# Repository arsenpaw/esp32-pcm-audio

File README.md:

# ESP32 WLED LED Driver

> **The active hardware is [`hardware/`](hardware/).** The earlier rev A design
> is kept read-only in [`hardware_deprecated/`](hardware_deprecated/) and is no longer maintained.

## Active board: `hardware/`

A WS2812B LED strip driver with:

- USB-C programming, a DC barrel jack, and screw-terminal inputs.
- Two strip outputs with a 74xx125 level shifter.
- A slide switch for 5 V or 12 V strips.
- A relay and a blade fuse.
- An SPH0641 PDM MEMS microphone (MK1).

We fit an **ESP32-S3-WROOM-1-N4** in the footprint drawn for the ESP32-S2-SOLO, because the S2
can't read PDM microphones. The pad-by-pad check is in [shop.md](shop.md).

### WLED pin map

| Function | GPIO |
|---|---|
| LED strip 1 data | 17 |
| LED strip 2 data | 21 |
| Relay | 7 |
| Status LED | 2 |
| Button (BOOT) | 0 |
| Microphone (PDM) | CLK 5, DATA 6 |

- KiCad project: `hardware/PCB/iot_led_strip_pcb.kicad_pro` (KiCad 10).
- Shopping list: [shop.md](shop.md). It uses the cheapest in-stock part for each line.
- Case: `hardware/case/`.

### Checks from the command line

```bash
kicad-cli sch erc hardware/PCB/iot_led_strip_pcb.kicad_sch
```

```bash
kicad-cli pcb drc hardware/PCB/iot_led_strip_pcb.kicad_pcb
```

On macOS, `kicad-cli` lives at `/Applications/KiCad/KiCad.app/Contents/MacOS/kicad-cli`.

## Deprecated: `hardware_deprecated/` (rev A)

This was the earlier design: a 66 × 32 mm, 4-layer, USB-C-only board.

- MCU: ESP32-S3-MINI-1.
- Power: a 2 A eFuse.
- Microphone: ICS-43434 I2S.

Its schematic is drawn and the board is routed, but it was never reviewed or ordered. These
documents belong to it:

- [Requirements & proposed design](docs/requirements/wled-audio-board.md)
- [WLED configuration](firmware/wled-config.md)

## Tooling

- **KiCad 10** (developed on 10.0.8).
- **KiCad MCP** for Claude Code:
  [`mixelpixx/KiCAD-MCP-Server`](https://github.com/mixelpixx/KiCAD-MCP-Server) v2.9.0.
  It's vendored as a git submodule at `tools/kicad-mcp-server` and registered in `.mcp.json`.
  One-time setup after cloning needs Node 18+ and KiCad 10 in `/Applications`:

  ```bash
  git submodule update --init
  ```

  ```bash
  ./scripts/setup-mcp.sh
  ```

  Launch Claude Code from the repo root, because `.mcp.json` uses paths relative to it.

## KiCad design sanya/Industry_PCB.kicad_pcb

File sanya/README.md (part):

# Система моніторингу технічного стану двигуна (вібрація / температура / тиск)

Навчальний прототип на окремому мікроконтролері **ATmega328P-AU**. Пристрій вимірює вібрацію (ADXL345), температуру (DS18B20) і тиск (аналоговий датчик 0–5 В), визначає стан NORMAL / WARNING / CRITICAL, сигналізує світлодіодами та зумером і **фізично вимикає навантаження через реле**. Додатково керує вентилятором охолодження (ШІМ).

> ⚠️ Це навчальний пристрій. Він **не сертифікований** для встановлення на реальний трактор чи інший транспортний засіб (немає захисту від load-dump, автомобільного температурного діапазону, випробувань на вібрацію/ЕМС).

## Файли

| Файл | Призначення |
|---|---|
| `Industry_PCB.kicad_pro` | проєкт KiCad 10 (класи кіл, правила DRC) |
| `Industry_PCB.kicad_sch` | принципова схема, 1 аркуш A3; усередині вузлів — провідники, між вузлами — іменовані мітки кіл. Резисторні збірки RN1 і RN2 показано окремими резисторами (RN1A…D, RN2A…D) біля своїх сигналів |
| `Industry_PCB.kicad_pcb` | двошарова плата 90 × 65 мм, повністю розведена |
| `Industry_PCB_schematic.pdf` | схема у PDF |
| `Industry_PCB_pcb.pdf` | плата у PDF (F.Cu, B.Cu, складальний шар) |
| `BOM.csv` | перелік компонентів (згрупований) |
| `_generator/` | Python-скрипти, якими згенеровано схему й плату (`design.py` — компоненти, `gen2.py` — поточна схема з провідниками, `place.py` — розміщення на платі) |
| `_old_ESP32_version/` | попередня версія проєкту (ESP32 DevKit + модулі), збережена без змін |

Проєкт створено у форматі **KiCad 10.0** (перевірено у 10.0.8). Під час першого запуску KiCad запропонує створити глобальні таблиці бібліотек — погодьтеся на стандартні; усі символи також вбудовані в сам файл схеми.

## Що змінено порівняно з попередньою версією

| Було | Стало |
|---|---|
| ESP32 DevKit (готова плата на двох гребінках) | окремий MCU ATmega328P-AU (TQFP-32) з кварцом, розв'язкою, ISP |
| SW-420 (цифровий «датчик вібрації», модуль) | 3-осьовий акселерометр ADXL345 на платі, I2C |
| модуль реле на 3-контактному роз'ємі | реле SRD-12VDC-SL-C на платі + драйвер ULN2003A + клеми NO/COM/NC |
| ACS712 (струм) | вхід тиску 0–5 В із захистом, дільником і RC-фільтром |
| живлення 5 В з гнізда, без захисту | 12 В → PTC → діод → TVS → L7805 (5 В) → MCP1700 (3,3 В) |
| немає вентилятора, кнопок, ISP, тест-точок | вихід вентилятора (ШІМ), RESET, ACK/SET, AVR-ISP-6, 9 тест-точок |

## Блоки схеми

1. **POWER.** Клема J1 (12 В) → самовідновлюваний запобіжник F1 (1,1 А) → діод Шотткі D1 (захист від переполюсування) → TVS D2 (SMBJ15CA) і C1 100 мкФ → L7805 (U1, 5 В) → MCP1700-3302 (U2, 3,3 В). Шина +12V живить лише реле, вентилятор і вхід стабілізатора.
2. **MCU.** ATmega328P-AU працює від **3,3 В на 8 МГц** (кварц Y1 + C6/C7 по 22 пФ). 16 МГц при 3,3 В виходить за межі специфікації, тому обрано 8 МГц; живлення 3,3 В дає пряме узгодження рівнів I2C з ADXL345 без перетворювача. C4/C5 — розв'язка VCC/AVCC, SW1 — RESET, RN2 — підтяжки.
3. **VIBRATION SENSOR.** ADXL345BCCZ (U4), I2C, адреса 0x53 (SDO → GND, CS → VDDIO). Живлення через феритову намистину FB1 і C8. Вихід INT1 заведено на PD2 (INT0). Мікросхема стоїть приблизно за 10 мм від кріпильного отвору H4 — плата кріпиться цим кутом до контрольованого вузла.
4. **TEMPERATURE SENSOR.** Роз'єм J3 (JST-XH, 3 конт.) для виносного DS18B20: 3V3 / DQ / GND. Підтяжка 4,7 кОм (RN2), ESD-діод D8 на лінії даних.
5. **PRESSURE INPUT.** Роз'єм J4: +5V / вхід / GND. Дільник R1/R2 (10k/18k, коефіцієнт 0,643: 5,0 В → 3,21 В), C9 100 нФ (зріз ≈ 250 Гц), BAT54S (D3) обмежує напругу до GND…3,3 В. R1 водночас обмежує струм при перенапрузі. Підходить будь-який датчик 0–5 В або 0,5–4,5 В (тиск оливи, гідравліка).
6. **DISPLAY.** Гніздо J5 під модуль OLED SSD1306 I2C (GND / VCC / SCL / SDA). Дисплей опційний.
7. **USER INTERFACE.** D4 зелений (NORMAL), D5 жовтий (WARNING), D6 червоний (CRITICAL), резисторна збірка RN1 4×330 Ом, кнопка SW2 ACK/SET (внутрішня підтяжка MCU).
8. **ALARM + драйвер.** ULN2003A (U5): канал 1 — реле, канал 2 — активний зумер BZ1 (5 В), канали 3–5 паралельно — вентилятор. Входи ULN мають вбудовані резистори на землю, тому під час скидання MCU всі виходи вимкнені. Вивід COM підключено до +12V — це вбудовані зворотні (flyback) діоди для котушки реле й вентилятора.
9. **RELAY / ACTUATOR.** Реле K1 (SPDT, котушка 12 В) і клема J6 NO/COM/NC. D7 показує стан реле. Логіка fail-safe: у нормі реле **увімкнене**, навантаження живиться через COM–NO; при аварії або зникненні живлення реле відпускає і розриває коло.
10. **FAN CONTROL.** Клема J7 (+12 В / FAN−), ШІМ із PD3 (OC2B) через три канали ULN2003A. Струм вентилятора до 0,6 А.
11. **PROGRAMMING.** Стандартний AVR-ISP-6 (J2).

Логіка роботи (для прошивки): температура висока → вентилятор; вібрація або тиск за критичним порогом → реле вимкнути + зумер + червоний LED; ACK скидає звукову сигналізацію.

## Розподіл виводів MCU (ATmega328P-AU, TQFP-32)

| Вивід | Порт | Коло | Призначення |
|---|---|---|---|
| 1 | PD3 (OC2B) | FAN_PWM | ШІМ вентилятора → U5 IN3–5 |
| 2 | PD4 | ONEWIRE_DQ | DS18B20 |
| 3, 5, 21 | GND | GND | |
| 4, 6 | VCC | +3V3 | розв'язка C4 |
| 7, 8 | PB6, PB7 | XTAL1, XTAL2 | кварц 8 МГц |
| 9 | PD5 | BUZZER_CTRL | зумер → U5 IN2 |
| 10 | PD6 | RELAY_CTRL | реле → U5 IN1, LED D7 |
| 11 | PD7 | BTN_ACK | кнопка ACK/SET (активний 0) |
| 12 | PB0 | LED_GREEN | NORMAL |
| 13 | PB1 | LED_YELLOW | WARNING |
| 14 | PB2 | LED_RED | CRITICAL |
| 15, 16, 17 | PB3, PB4, PB5 | MOSI, MISO, SCK | ISP |
| 18 | AVCC | +3V3 | розв'язка C5, опорна напруга АЦП |
| 23 | PC0 (ADC0) | PRESS_ADC | тиск |
| 27, 28 | PC4, PC5 | SDA, SCL | ADXL345, OLED |
| 29 | PC6 | RESET | SW1, ISP, підтяжка 4,7 кОм |
| 30, 31 | PD0, PD1 | UART_RX, UART_TX | тест-точки TP8, TP9 (налагодження) |
| 32 | PD2 (INT0) | ADXL_INT1 | переривання акселерометра |
| 19, 20, 22, 24–26 | ADC6, AREF, ADC7, PC1–PC3 | — | не використані (резерв) |

Тиск у вольтах на вході: `Vin = ADC / 1023 × 3,3 В / 0,643`.

## Розподіл компонентів: 40 шт.

| Блок | К-сть | Компоненти |
|---|---|---|
| POWER | 9 | C1, C2, C3, D1, D2, F1, J1, U1, U2 |
| MCU | 8 | C4, C5, C6, C7, RN2, SW1, U3, Y1 |
| VIBRATION | 3 | C8, FB1, U4 |
| TEMPERATURE | 2 | D8, J3 |
| PRESSURE | 5 | C9, D3, J4, R1, R2 |
| DISPLAY | 1 | J5 |
| USER INTERFACE | 5 | D4, D5, D6, RN1, SW2 |
| ALARM | 2 | BZ1, U5 |
| RELAY / ACTUATOR | 3 | D7, J6, K1 |
| FAN CONTROL | 1 | J7 |
| PROGRAMMING | 1 | J2 |
| **Разом** | **40** | |

Тест-точки TP1–TP9 і кріпильні отвори H1–H4 — це лише мідні площадки та отвори, у BOM і підрахунок вони не входять. Щоб вкластися в 40 компонентів при повному наборі функцій, резистори світлодіодів і підтяжок зібрано у дві збірки 4×0603, а три транзисторні ключі з діодами замінено однією ULN2003A.

## Перелік компонентів

| Ref | Value | Footprint | MPN | Виробник | Блок |
|---|---|---|---|---|---|
| BZ1 | Buzzer 5V active | Buzzer_12x9.5RM7.6 | TMB12A05 | generic 12x9.5 mm | ALARM |
| C1 | 100uF/35V | CP_Radial_D6.3mm_P2.50mm | ECA-1VM101 | Panasonic | POWER |
| C2 | 10uF/16V | C_0805_2012Metric | CL21A106KOQNNNE | Samsung | POWER |
| C3 | 1uF/16V | C_0603_1608Metric | CL10A105KO8NNNC | Samsung | POWER |
| C4 | 100nF | C_0603_1608Metric | CL10B104KB8NNNC | Samsung | MCU |
| C5 | 100nF | C_0603_1608Metric | CL10B104KB8NNNC | Samsung | MCU |
| C6 | 22pF | C_0603_1608Metric | CL10C220JB8NNNC | Samsung | MCU |
| C7 | 22pF | C_0603_1608Metric | CL10C220JB8NNNC | Samsung | MCU |
| C8 | 100nF | C_0603_1608Metric | CL10B104KB8NNNC | Samsung | VIBRATION |
| C9 | 100nF | C_0603_1608Metric | CL10B104KB8NNNC | Samsung | PRESSURE |
| D1 | SS34 | D_SMA | SS34 | onsemi / MCC | POWER |
| D2 | SMBJ15CA | D_SMB | SMBJ15CA | Littelfuse | POWER |
| D3 | BAT54S | SOT-23 | BAT54S,215 | Nexperia | PRESSURE |
| D4 | GREEN | LED_0805_2012Metric | APT2012SGC | Kingbright | USER INTERFACE |
| D5 | YELLOW | LED_0805_2012Metric | APT2012SYCK | Kingbright | USER INTERFACE |
| D6 | RED | LED_0805_2012Metric | APT2012SRCPRV | Kingbright | USER INTERFACE |
| D7 | ORANGE (RELAY ON) | LED_0805_2012Metric | APT2012SECK | Kingbright | RELAY / ACTUATOR |
| D8 | PESD5V0S1BA | D_SOD-323 | PESD5V0S1BA,115 | Nexperia | TEMPERATURE |
| F1 | 1.1A/16V PTC | Fuse_1812_4532Metric_Pad1.30x3.40mm_HandSolder | MF-MSMF110/16-2 | Bourns | POWER |
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
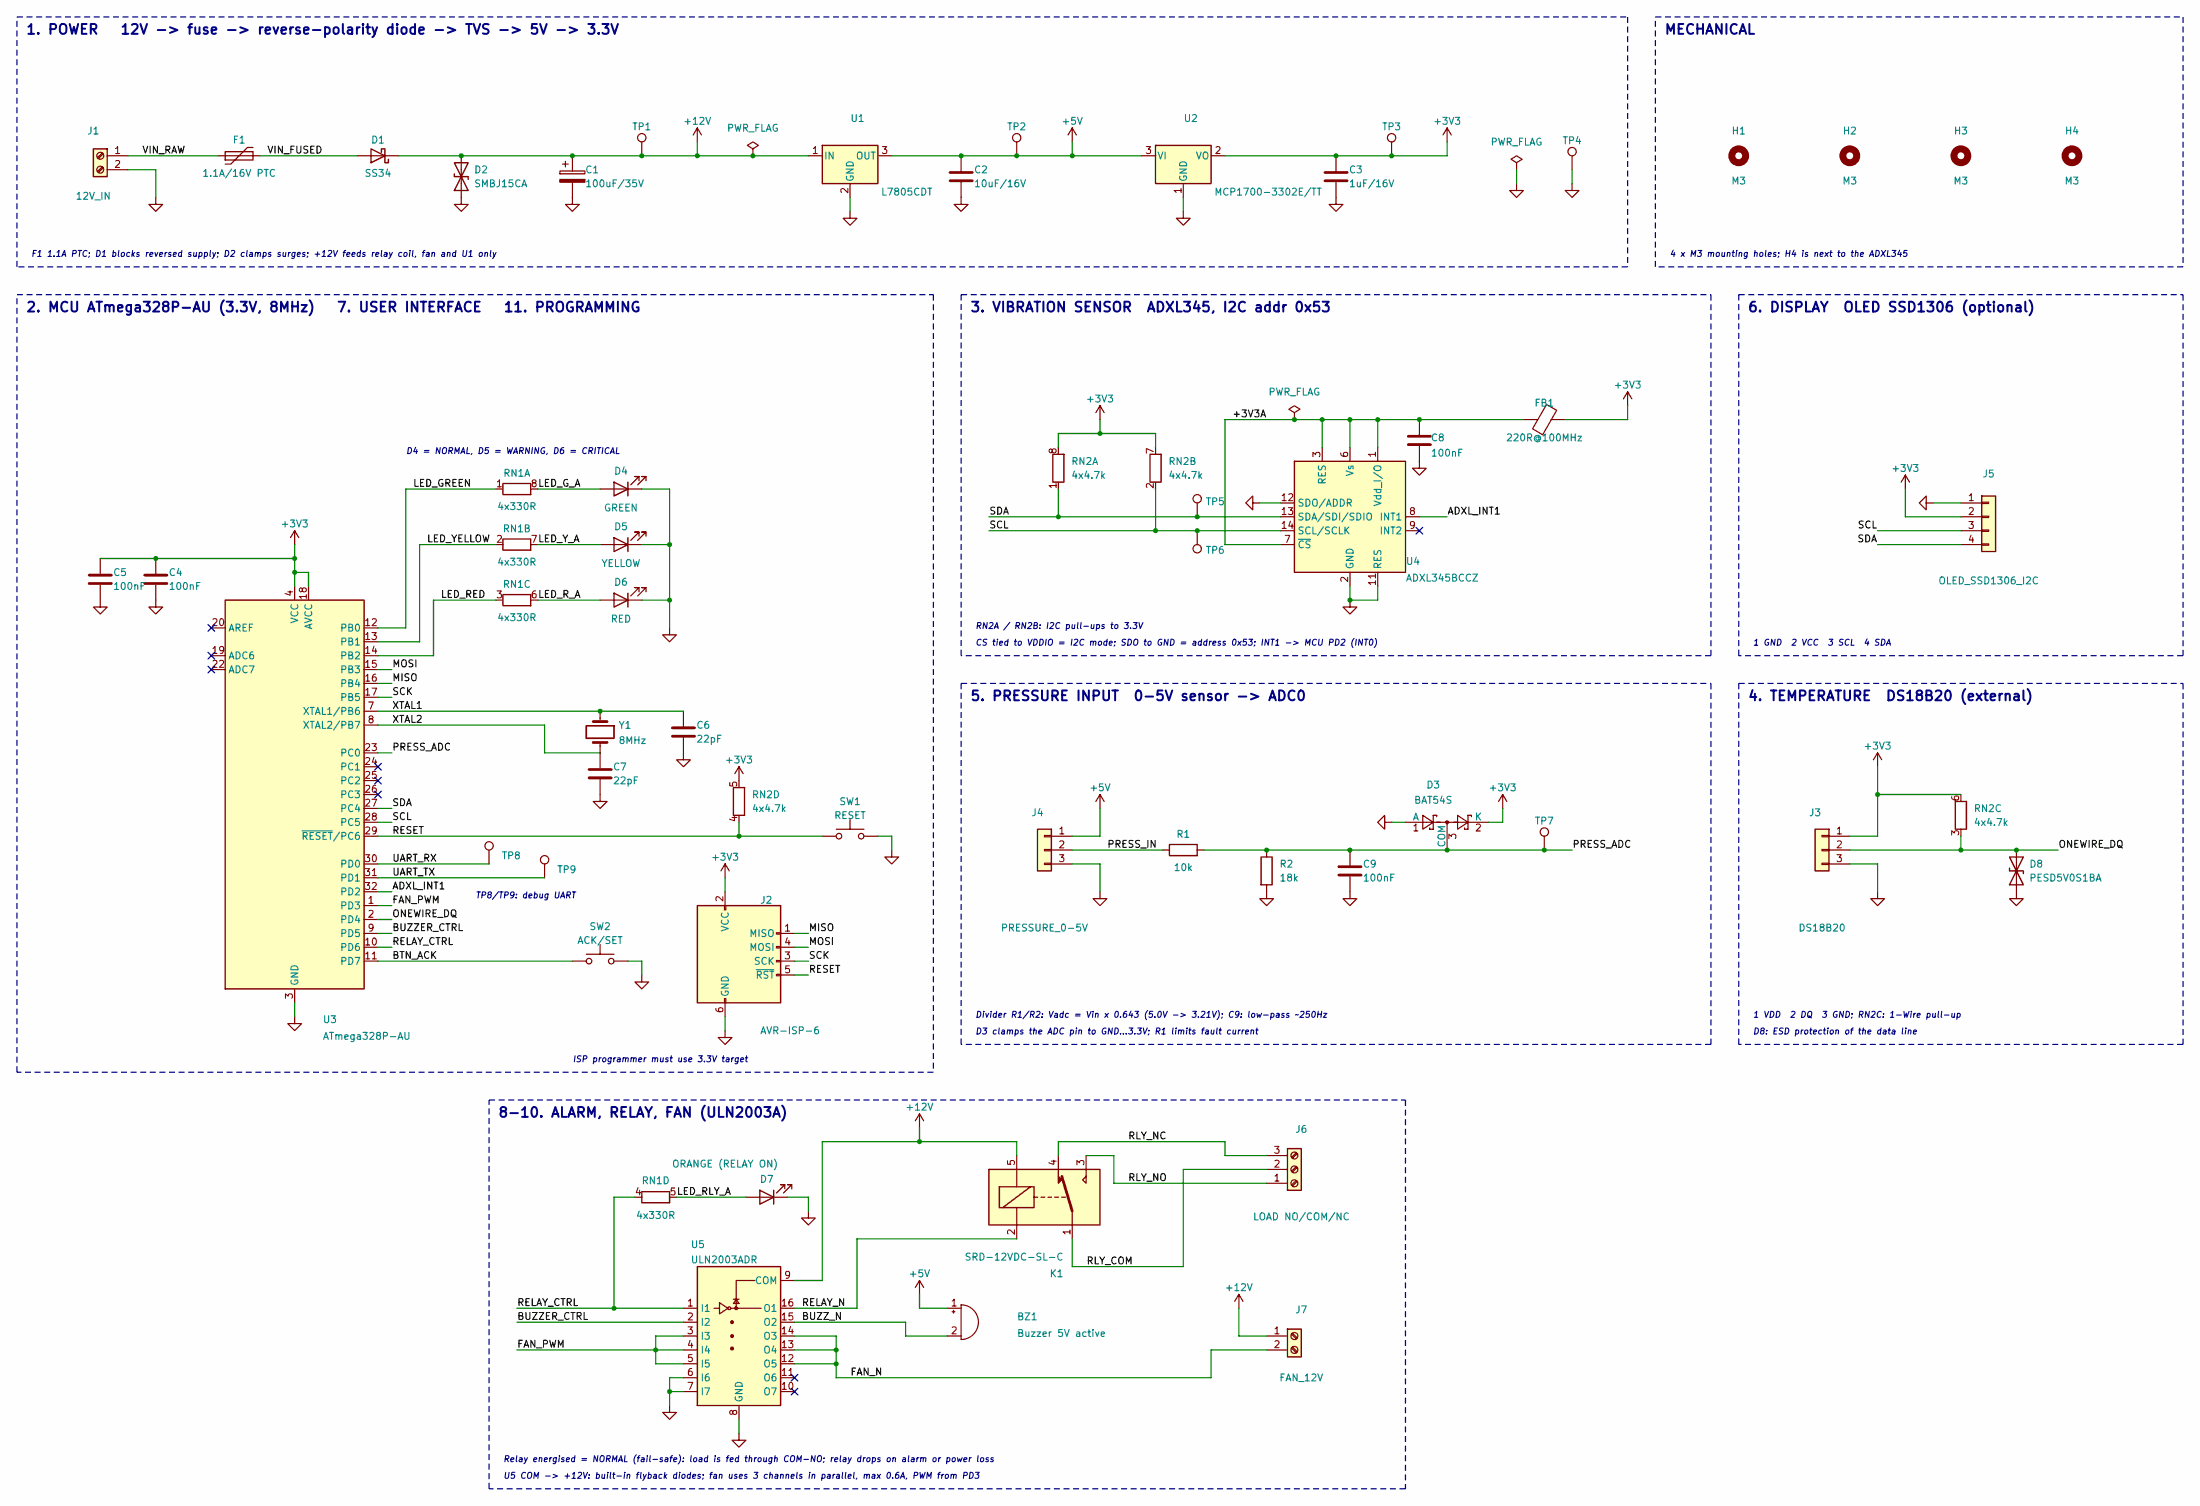
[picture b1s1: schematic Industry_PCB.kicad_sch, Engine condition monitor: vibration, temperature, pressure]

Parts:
BZ1: Buzzer 5V active; Buzzer_12x9.5RM7.6; MPN TMB12A05
C1: 100uF/35V; CP_Radial_D6.3mm_P2.50mm; MPN ECA-1VM101
C2: 10uF/16V; C_0805_2012Metric; MPN CL21A106KOQNNNE
C3: 1uF/16V; C_0603_1608Metric; MPN CL10A105KO8NNNC
C4, C5, C8, C9: 100nF; C_0603_1608Metric; MPN CL10B104KB8NNNC
C6, C7: 22pF; C_0603_1608Metric; MPN CL10C220JB8NNNC
D1: SS34; D_SMA; MPN SS34
D2: SMBJ15CA; D_SMB; MPN SMBJ15CA
D3: BAT54S; SOT-23; MPN BAT54S,215
D4: GREEN; LED_0805_2012Metric; MPN APT2012SGC
D5: YELLOW; LED_0805_2012Metric; MPN APT2012SYCK
D6: RED; LED_0805_2012Metric; MPN APT2012SRCPRV
D7: ORANGE (RELAY ON); LED_0805_2012Metric; MPN APT2012SECK
D8: PESD5V0S1BA; D_SOD-323; MPN PESD5V0S1BA,115
F1: 1.1A/16V PTC; Fuse_1812_4532Metric_Pad1.30x3.40mm_HandSolder; MPN MF-MSMF110/16-2
FB1: 220R@100MHz; L_0603_1608Metric; MPN BLM18PG221SN1D
H1, H2, H3, H4: M3; MountingHole_3.2mm_M3
J1: 12V_IN; TerminalBlock_Phoenix_MKDS-1,5-2-5.08_1x02_P5.08mm_Horizont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; MPN MKDS 1,5/2-5,08 (1715721)
J2: AVR-ISP-6; PinHeader_2x03_P2.54mm_Vertical; MPN PRPC003DAAN-RC
J3: DS18B20; JST_XH_B3B-XH-A_1x03_P2.50mm_Vertical; MPN B3B-XH-A
J4: PRESSURE_0-5V; JST_XH_B3B-XH-A_1x03_P2.50mm_Vertical; MPN B3B-XH-A
J5: OLED_SSD1306_I2C; PinSocket_1x04_P2.54mm_Vertical; MPN PPTC041LFBN-RC
J6: LOAD NO/COM/NC; TerminalBlock_Phoenix_MKDS-1,5-3-5.08_1x03_P5.08mm_Horizont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; MPN MKDS 1,5/3-5,08 (1715734)
J7: FAN_12V; TerminalBlock_Phoenix_MKDS-1,5-2-5.08_1x02_P5.08mm_Horizont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; MPN MKDS 1,5/2-5,08 (1715721)
K1: SRD-12VDC-SL-C; Relay_SPDT_SANYOU_SRD_Series_Form_C; MPN SRD-12VDC-SL-C
R1: 10k; R_0603_1608Metric; MPN RC0603FR-0710KL
R2: 18k; R_0603_1608Metric; MPN RC0603FR-0718KL
RN1: 4x330R; R_Array_Convex_4x0603; MPN YC164-JR-07330RL
RN2: 4x4.7k; R_Array_Convex_4x0603; MPN YC164-JR-074K7L
SW1: RESET; SW_PUSH_6mm; MPN B3F-1000
SW2: ACK/SET; SW_PUSH_6mm; MPN B3F-1000
TP1: +12V; TestPoint_Pad_D1.5mm
TP2: +5V; TestPoint_Pad_D1.5mm
TP3: +3V3; TestPoint_Pad_D1.5mm
TP4: GND; TestPoint_Pad_D1.5mm
TP5: SDA; TestPoint_Pad_D1.5mm
TP6: SCL; TestPoint_Pad_D1.5mm
TP7: PRESS_ADC; TestPoint_Pad_D1.5mm
TP8: UART_RX; TestPoint_Pad_D1.5mm
TP9: UART_TX; TestPoint_Pad_D1.5mm
U1: L7805CDT; TO-252-2; MPN L7805CDT-TR
U2: MCP1700-3302E/TT; SOT-23; MPN MCP1700T-3302E/TT
U3: ATmega328P-AU; TQFP-32_7x7mm_P0.8mm; MPN ATMEGA328P-AU
U4: ADXL345BCCZ; LGA-14_3x5mm_P0.8mm_LayoutBorder1x6y; MPN ADXL345BCCZ-RL7
U5: ULN2003ADR; SOIC-16_3.9x9.9mm_P1.27mm; MPN ULN2003ADR
Y1: 8MHz; Crystal_SMD_HC49-SD; MPN ABLS-8.000MHZ-B4-T

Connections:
+3V3: C3.1, C4.1, C5.1, D3.2 (K), FB1.1, J2.2 (VCC), J3.1, J5.2, RN2.5 (R4.2), RN2.6 (R3.2), RN2.7 (R2.2), RN2.8 (R1.2), TP3.1 (1_1), U2.2 (VO), U3.4 (VCC), U3.6 (VCC), U3.18 (AVCC)
+5V: BZ1.1 (+), C2.1, J4.1, TP2.1 (1_1), U1.3 (OUT), U2.3 (VI)
+12V: C1.1, D1.1 (K), D2.2 (A2), J7.1, K1.5, TP1.1 (1_1), U1.1 (IN), U5.9 (COM)
/+3V3A: C8.1, FB1.2, U4.1 (Vdd_I/O), U4.3 (RES), U4.6 (Vs), U4.7 (~CS)
/ADXL_INT1: U3.32 (PD2), U4.8 (INT1)
/BTN_ACK: SW2.1, U3.11 (PD7)
/BUZZER_CTRL: U3.9 (PD5), U5.2 (I2)
/BUZZ_N: BZ1.2 (-), U5.15 (O2)
/FAN_N: J7.2, U5.12 (O5), U5.13 (O4), U5.14 (O3)
/FAN_PWM: U3.1 (PD3), U5.3 (I3), U5.4 (I4), U5.5 (I5)
/LED_GREEN: RN1.1 (R1.1), U3.12 (PB0)
/LED_G_A: D4.2 (A), RN1.8 (R1.2)
/LED_RED: RN1.3 (R3.1), U3.14 (PB2)
/LED_RLY_A: D7.2 (A), RN1.5 (R4.2)
/LED_R_A: D6.2 (A), RN1.6 (R3.2)
/LED_YELLOW: RN1.2 (R2.1), U3.13 (PB1)
/LED_Y_A: D5.2 (A), RN1.7 (R2.2)
/MISO: J2.1 (MISO), U3.16 (PB4)
/MOSI: J2.4 (MOSI), U3.15 (PB3)
/ONEWIRE_DQ: D8.2 (A2), J3.2, RN2.3 (R3.1), U3.2 (PD4)
/PRESS_ADC: C9.1, D3.3 (COM), R1.2, R2.1, TP7.1 (1_1), U3.23 (PC0)
/PRESS_IN: J4.2, R1.1
/RELAY_CTRL: RN1.4 (R4.1), U3.10 (PD6), U5.1 (I1)
/RELAY_N: K1.2, U5.16 (O1)
/RESET: J2.5 (~RST), RN2.4 (R4.1), SW1.1, U3.29 (~RESET/PC6)
/RLY_COM: J6.2, K1.1
/RLY_NC: J6.3, K1.4
/RLY_NO: J6.1, K1.3
/SCK: J2.3 (SCK), U3.17 (PB5)
/SCL: J5.3, RN2.2 (R2.1), TP6.1 (1_1), U3.28 (PC5), U4.14 (SCL/SCLK)
/SDA: J5.4, RN2.1 (R1.1), TP5.1 (1_1), U3.27 (PC4), U4.13 (SDA/SDI/SDIO)
/UART_RX: TP8.1 (1_1), U3.30 (PD0)
/UART_TX: TP9.1 (1_1), U3.31 (PD1)
/VIN_FUSED: D1.2 (A), F1.2
/VIN_RAW: F1.1, J1.1
/XTAL1: C6.1, U3.7 (XTAL1/PB6), Y1.1
/XTAL2: C7.1, U3.8 (XTAL2/PB7), Y1.2
GND: C1.2, C2.2, C3.2, C4.2, C5.2, C6.2, C7.2, C8.2, C9.2, D2.1 (A1), D3.1 (A), D4.1 (K), D5.1 (K), D6.1 (K), D7.1 (K), D8.1 (A1), J1.2, J2.6 (GND), J3.3, J4.3, J5.1, R2.2, SW1.2, SW2.2, TP4.1 (1_1), U1.2 (GND), U2.1 (GND), U3.3 (GND), U3.5 (GND), U3.21 (GND), U4.2 (GND), U4.4 (GND), U4.5 (GND), U4.11 (RES), U4.12 (SDO/ADDR), U5.6 (I6), U5.7 (I7), U5.8 (GND)

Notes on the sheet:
1. POWER 12V -> fuse -> reverse-polarity diode -> TVS -> 5V -> 3.3V
F1 1.1A PTC; D1 blocks reversed supply; D2 clamps surges; +12V feeds relay coil, fan and U1 only
MECHANICAL
4 x M3 mounting holes; H4 is next to the ADXL345
2. MCU ATmega328P-AU (3.3V, 8MHz) 7. USER INTERFACE 11. PROGRAMMING
D4 = NORMAL, D5 = WARNING, D6 = CRITICAL
ISP programmer must use 3.3V target
TP8/TP9: debug UART
3. VIBRATION SENSOR ADXL345, I2C addr 0x53
CS tied to VDDIO = I2C mode; SDO to GND = address 0x53; INT1 -> MCU PD2 (INT0)
RN2A / RN2B: I2C pull-ups to 3.3V
6. DISPLAY OLED SSD1306 (optional)
1 GND 2 VCC 3 SCL 4 SDA
5. PRESSURE INPUT 0-5V sensor -> ADC0
Divider R1/R2: Vadc = Vin x 0.643 (5.0V -> 3.21V); C9: low-pass ~250Hz
D3 clamps the ADC pin to GND...3.3V; R1 limits fault current
4. TEMPERATURE DS18B20 (external)
1 VDD 2 DQ 3 GND; RN2C: 1-Wire pull-up
D8: ESD protection of the data line
8-10. ALARM, RELAY, FAN (ULN2003A)
Relay energised = NORMAL (fail-safe): load is fed through COM-NO; relay drops on alarm or power loss
U5 COM -> +12V: built-in flyback diodes; fan uses 3 channels in parallel, max 0.6A, PWM from PD3

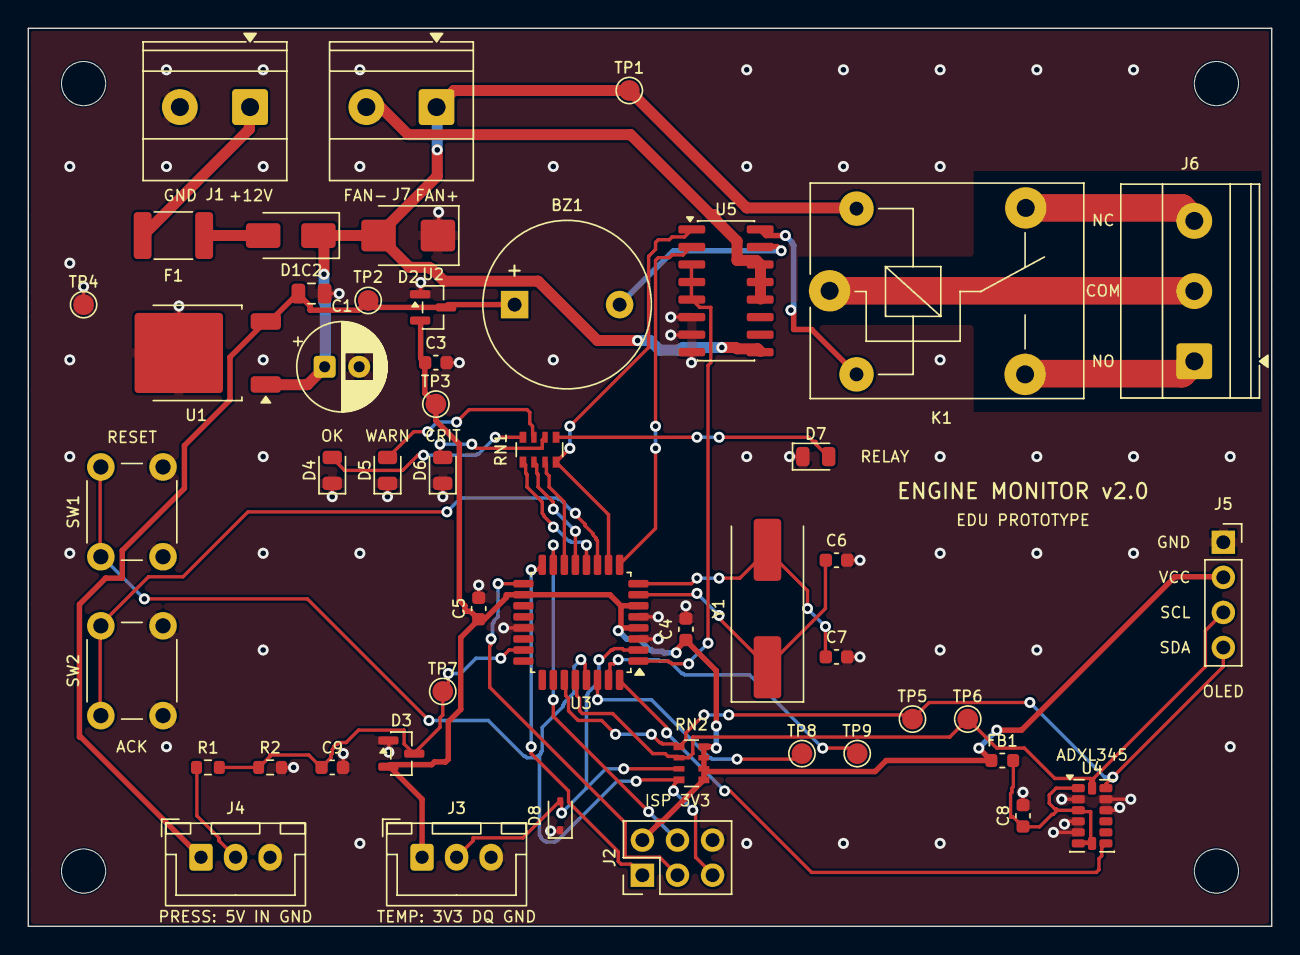
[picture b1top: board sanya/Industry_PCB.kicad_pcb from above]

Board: 2 copper layers, 90.0 x 65.0 mm, 53 parts (0 on the bottom side), 38 nets.

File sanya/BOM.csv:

Item,Qty,Reference,Value,Footprint,MPN,Manufacturer
1,1,BZ1,Buzzer 5V active,Buzzer_Beeper:Buzzer_12x9.5RM7.6,TMB12A05,generic 12x9.5 mm
2,1,C1,100uF/35V,Capacitor_THT:CP_Radial_D6.3mm_P2.50mm,ECA-1VM101,Panasonic
3,1,C2,10uF/16V,Capacitor_SMD:C_0805_2012Metric,CL21A106KOQNNNE,Samsung
4,1,C3,1uF/16V,Capacitor_SMD:C_0603_1608Metric,CL10A105KO8NNNC,Samsung
5,4,C4 C5 C8 C9,100nF,Capacitor_SMD:C_0603_1608Metric,CL10B104KB8NNNC,Samsung
6,2,C6 C7,22pF,Capacitor_SMD:C_0603_1608Metric,CL10C220JB8NNNC,Samsung
7,1,D1,SS34,Diode_SMD:D_SMA,SS34,onsemi / MCC
8,1,D2,SMBJ15CA,Diode_SMD:D_SMB,SMBJ15CA,Littelfuse
9,1,D3,BAT54S,Package_TO_SOT_SMD:SOT-23,"BAT54S,215",Nexperia
10,1,D4,GREEN,LED_SMD:LED_0805_2012Metric,APT2012SGC,Kingbright
11,1,D5,YELLOW,LED_SMD:LED_0805_2012Metric,APT2012SYCK,Kingbright
12,1,D6,RED,LED_SMD:LED_0805_2012Metric,APT2012SRCPRV,Kingbright
13,1,D7,ORANGE (RELAY ON),LED_SMD:LED_0805_2012Metric,APT2012SECK,Kingbright
14,1,D8,PESD5V0S1BA,Diode_SMD:D_SOD-323,"PESD5V0S1BA,115",Nexperia
15,1,F1,1.1A/16V PTC,Fuse:Fuse_1812_4532Metric_Pad1.30x3.40mm_HandSolder,MF-MSMF110/16-2,Bourns
16,1,FB1,220R@100MHz,Inductor_SMD:L_0603_1608Metric,BLM18PG221SN1D,Murata
17,1,J1,12V_IN,"TerminalBlock_Phoenix:TerminalBlock_Phoenix_MKDS-1,5-2-5.08_1x02_P5.08mm_Horizontal","MKDS 1,5/2-5,08 (1715721)",Phoenix Contact
18,1,J2,AVR-ISP-6,Connector_PinHeader_2.54mm:PinHeader_2x03_P2.54mm_Vertical,PRPC003DAAN-RC,Sullins
19,1,J3,DS18B20,Connector_JST:JST_XH_B3B-XH-A_1x03_P2.50mm_Vertical,B3B-XH-A,JST
20,1,J4,PRESSURE_0-5V,Connector_JST:JST_XH_B3B-XH-A_1x03_P2.50mm_Vertical,B3B-XH-A,JST
21,1,J5,OLED_SSD1306_I2C,Connector_PinSocket_2.54mm:PinSocket_1x04_P2.54mm_Vertical,PPTC041LFBN-RC,Sullins
22,1,J6,LOAD NO/COM/NC,"TerminalBlock_Phoenix:TerminalBlock_Phoenix_MKDS-1,5-3-5.08_1x03_P5.08mm_Horizontal","MKDS 1,5/3-5,08 (1715734)",Phoenix Contact
23,1,J7,FAN_12V,"TerminalBlock_Phoenix:TerminalBlock_Phoenix_MKDS-1,5-2-5.08_1x02_P5.08mm_Horizontal","MKDS 1,5/2-5,08 (1715721)",Phoenix Contact
24,1,K1,SRD-12VDC-SL-C,Relay_THT:Relay_SPDT_SANYOU_SRD_Series_Form_C,SRD-12VDC-SL-C,Songle / Sanyou
25,1,R1,10k,Resistor_SMD:R_0603_1608Metric,RC0603FR-0710KL,Yageo
26,1,R2,18k,Resistor_SMD:R_0603_1608Metric,RC0603FR-0718KL,Yageo
27,1,RN1,4x330R,Resistor_SMD:R_Array_Convex_4x0603,YC164-JR-07330RL,Yageo
28,1,RN2,4x4.7k,Resistor_SMD:R_Array_Convex_4x0603,YC164-JR-074K7L,Yageo
29,1,SW1,RESET,Button_Switch_THT:SW_PUSH_6mm,B3F-1000,Omron
30,1,SW2,ACK/SET,Button_Switch_THT:SW_PUSH_6mm,B3F-1000,Omron
31,1,U1,L7805CDT,Package_TO_SOT_SMD:TO-252-2,L7805CDT-TR,STMicroelectronics
32,1,U2,MCP1700-3302E/TT,Package_TO_SOT_SMD:SOT-23,MCP1700T-3302E/TT,Microchip
33,1,U3,ATmega328P-AU,Package_QFP:TQFP-32_7x7mm_P0.8mm,ATMEGA328P-AU,Microchip
34,1,U4,ADXL345BCCZ,Package_LGA:LGA-14_3x5mm_P0.8mm_LayoutBorder1x6y,ADXL345BCCZ-RL7,Analog Devices
35,1,U5,ULN2003ADR,Package_SO:SOIC-16_3.9x9.9mm_P1.27mm,ULN2003ADR,Texas Instruments
36,1,Y1,8MHz,Crystal:Crystal_SMD_HC49-SD,ABLS-8.000MHZ-B4-T,Abracon

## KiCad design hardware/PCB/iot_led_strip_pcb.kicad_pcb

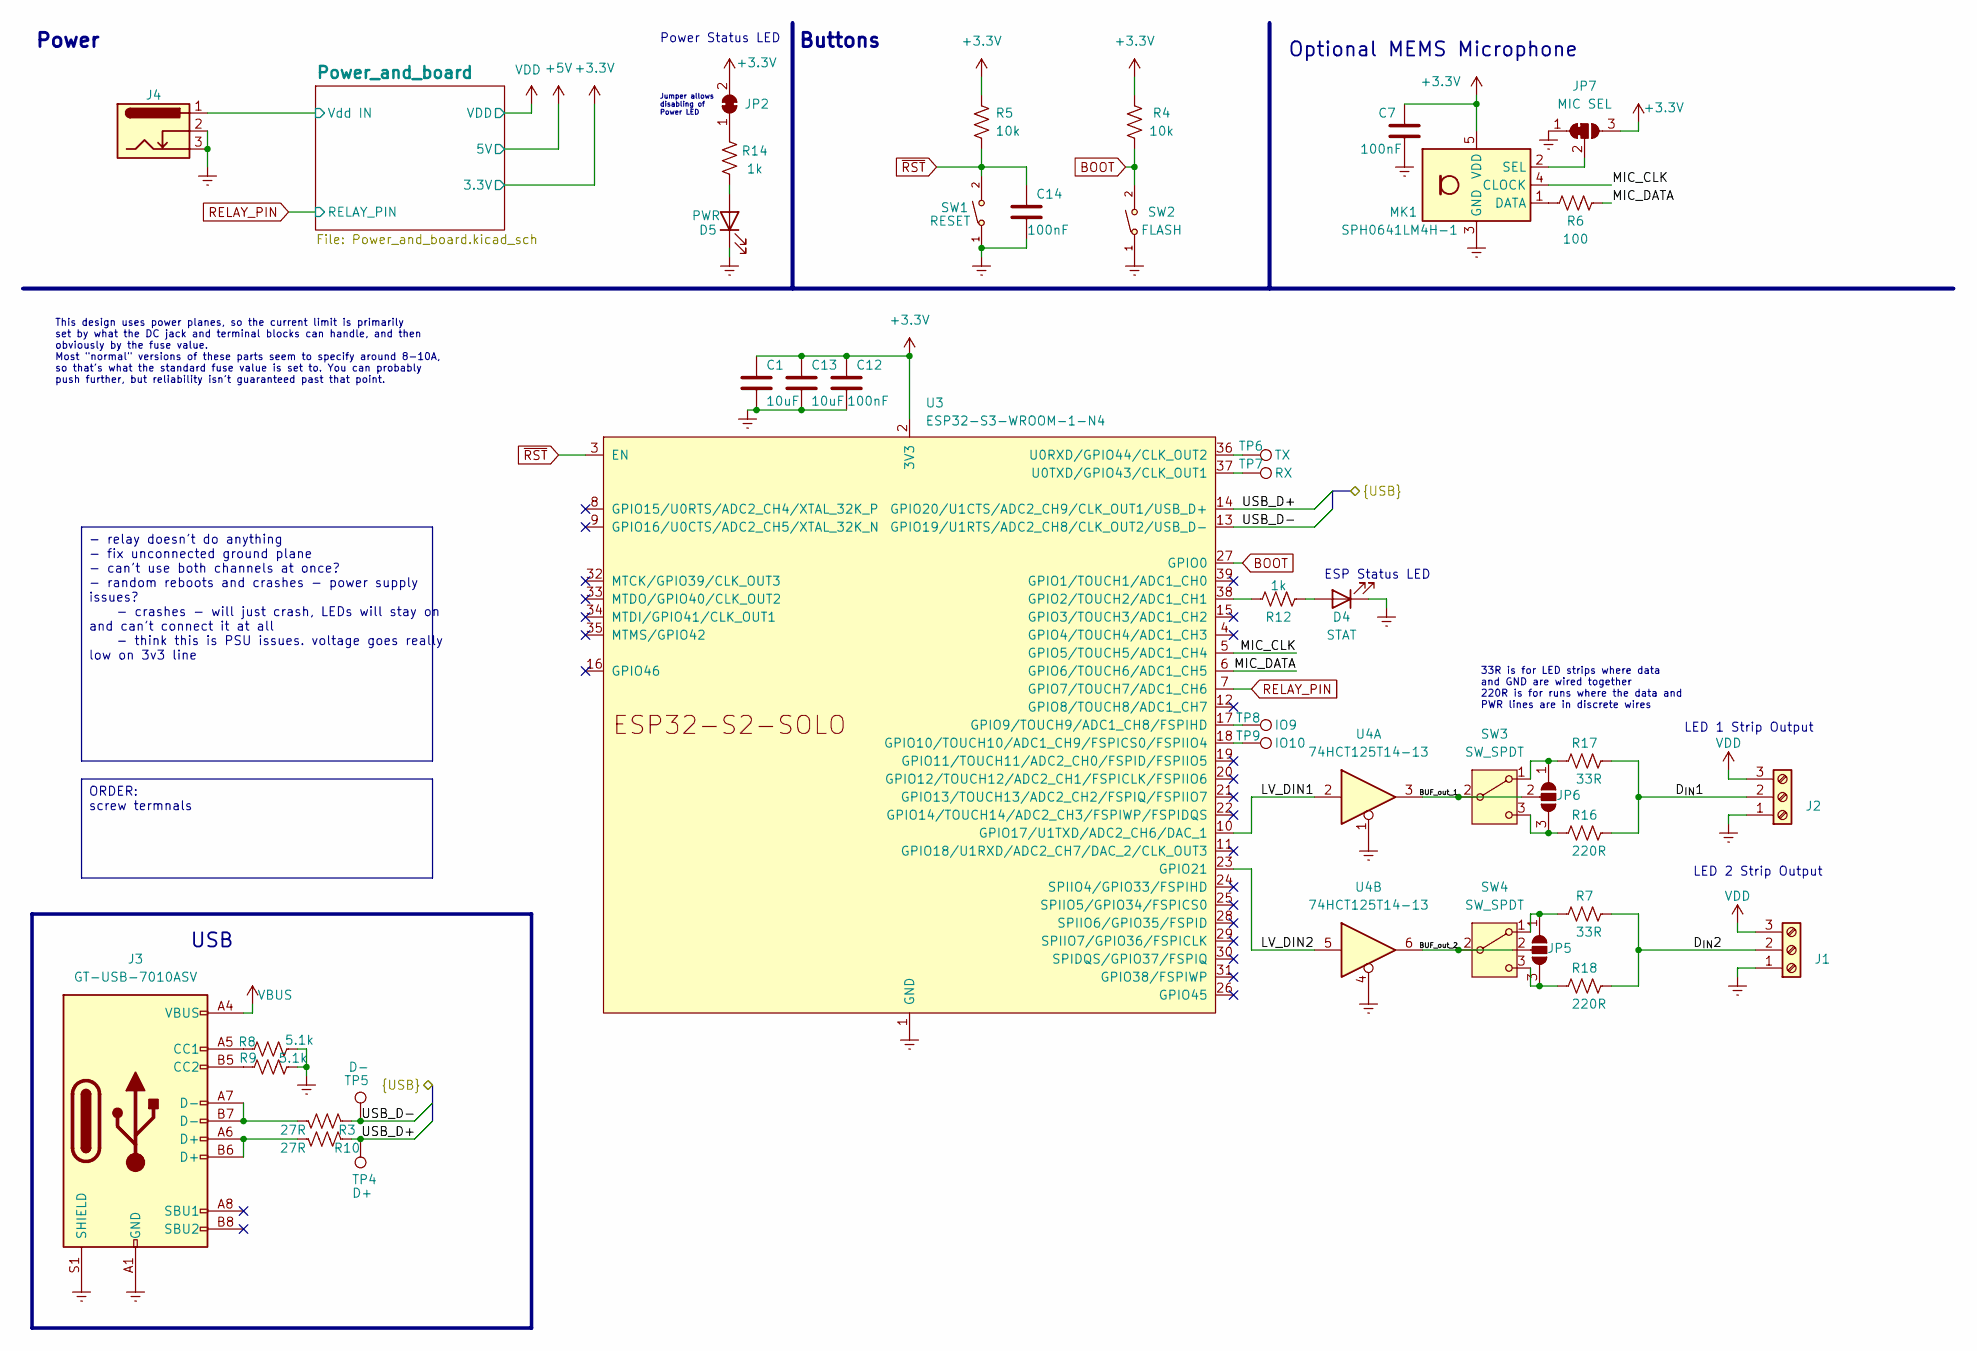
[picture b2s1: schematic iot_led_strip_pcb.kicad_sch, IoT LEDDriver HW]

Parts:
C1, C13: 10uF; C_0805_2012Metric_Pad1.18x1.45mm_HandSolder; LCSC C15850
C7, C12, C14: 100nF; C_0805_2012Metric_Pad1.18x1.45mm_HandSolder; LCSC C49678
D4: STAT; LED_0805_2012Metric_Pad1.15x1.40mm_HandSolder; LCSC C2297
D5: PWR; LED_0805_2012Metric_Pad1.15x1.40mm_HandSolder; LCSC C84256
J1, J2: Screw_Terminal_01x03; TerminalBlock_bornier-3_P5.08mm; LCSC C500022
J3: GT-USB-7010ASV; USB-C-GT7010_FIXED; LCSC C2988369
J4: Barrel_Jack_Switch_Pin3Ring; BarrelJack_Wuerth_6941xx301002
JP2: PWR_LED_BRIDGE; SolderJumper-2_P1.3mm_Bridged_RoundedPad1.0x1.5mm
JP5, JP6: SolderJumper_3_Open; SolderJumper-3_P1.3mm_Open_Pad1.0x1.5mm
JP7: MIC SEL; SolderJumper-3_P1.3mm_Bridged12_RoundedPad1.0x1.5mm
MK1: SPH0641LM4H-1; Knowles_LGA-5_3.5x2.65mm; LCSC C497724
R3, R10: 27R; R_0805_2012Metric_Pad1.20x1.40mm_HandSolder; LCSC C17594
R4, R5: 10k; R_0805_2012Metric_Pad1.20x1.40mm_HandSolder; LCSC C17414
R6: 100; R_0805_2012Metric_Pad1.20x1.40mm_HandSolder; LCSC C17408
R7, R17: 33R; R_0805_2012Metric_Pad1.20x1.40mm_HandSolder; LCSC C17634
R8, R9: 5.1k; R_0805_2012Metric_Pad1.20x1.40mm_HandSolder; LCSC C27834
R12, R14: 1k; R_0805_2012Metric_Pad1.20x1.40mm_HandSolder; LCSC C17513
R16, R18: 220R; R_0805_2012Metric_Pad1.20x1.40mm_HandSolder; LCSC C17557
SW1: RESET; SW_SPST_TL3342; LCSC C318884
SW2: FLASH; SW_SPST_TL3342; LCSC C318884
SW3, SW4: SW_SPDT; SW_SPDT_PCM12; LCSC C319020
TP4: D+; TestPoint_Pad_D1.5mm
TP5: D-; TestPoint_Pad_D1.5mm
TP6: TX; TestPoint_Pad_D1.5mm
TP7: RX; TestPoint_Pad_D1.5mm
TP8: IO9; TestPoint_Pad_D1.5mm
TP9: IO10; TestPoint_Pad_D1.5mm
U3: ESP32-S3-WROOM-1-N4; ESP32-S2-SOLO; LCSC C2913197
U4: 74HCT125T14-13; TSSOP-14_4.4x5mm_P0.65mm; LCSC C842453

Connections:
+3.3V: C1.1, C7.1, C12.1, C13.1, JP2.2 (B), JP7.3 (B), MK1.5 (VDD), R4.2, R5.1, U3.2 (3V3); also elsewhere on the board
/BUF_out_1: JP6.2 (C), SW3.2 (B), U4.3
/BUF_out_2: JP5.2 (C), SW4.2 (B), U4.6
/D_{IN}1: J2.2, R16.2, R17.2
/D_{IN}2: J1.2, R7.2, R18.2
/LV_DIN1: U3.10 (GPIO17/U1TXD/ADC2_CH6/DAC_1), U4.2
/LV_DIN2: U3.23 (GPIO21), U4.5
/MIC_CLK: MK1.4 (CLOCK), U3.5 (GPIO5/TOUCH5/ADC1_CH4)
/MIC_DATA: R6.1, U3.6 (GPIO6/TOUCH6/ADC1_CH5)
/Power_and_board/Vdd IN: J4.1; also elsewhere on the board
/USB_D+: R10.2, TP4.1, U3.14 (GPIO20/U1CTS/ADC2_CH9/CLK_OUT1/USB_D+)
/USB_D-: R3.2, TP5.1, U3.13 (GPIO19/U1RTS/ADC2_CH8/CLK_OUT2/USB_D-)
BOOT: R4.1, SW2.2, U3.27 (GPIO0)
Earth: C1.2, C7.2, C12.2, C13.2, C14.2, D4.1 (K), D5.1 (K), J1.1, J2.1, J3.A1 (GND), J3.A12 (GND), J3.B1 (GND), J3.B12 (GND), J3.S1 (SHIELD), J4.2, J4.3, JP7.1 (A), MK1.3 (GND), R8.2, R9.1, SW1.1, SW2.1, U3.1 (GND), U3.40 (GND), U3.41 (GND), U4.1, U4.4; also elsewhere on the board
unnamed: D4.2 (A), R12.1
unnamed: D5.2 (A), R14.1
unnamed: J3.A5 (CC1), R8.1
unnamed: J3.B5 (CC2), R9.2
unnamed: J3.A6 (D+), J3.B6 (D+), R10.1
unnamed: J3.A7 (D-), J3.B7 (D-), R3.1
unnamed: JP2.1 (A), R14.2
unnamed: JP5.1 (A), R7.1, SW4.1 (A)
unnamed: JP5.3 (B), R18.1, SW4.3 (C)
unnamed: JP6.1 (A), R17.1, SW3.1 (A)
unnamed: JP6.3 (B), R16.1, SW3.3 (C)
unnamed: JP7.2 (C), MK1.2 (SEL)
unnamed: MK1.1 (DATA), R6.2
unnamed: R12.2, U3.38 (GPIO2/TOUCH2/ADC1_CH1)
unnamed: TP8.1, U3.17 (GPIO9/TOUCH9/ADC1_CH8/FSPIHD)
unnamed: TP9.1, U3.18 (GPIO10/TOUCH10/ADC1_CH9/FSPICS0/FSPIIO4)
unnamed: TP6.1, U3.36 (U0RXD/GPIO44/CLK_OUT2)
unnamed: TP7.1, U3.37 (U0TXD/GPIO43/CLK_OUT1)
RELAY_PIN: U3.7 (GPIO7/TOUCH7/ADC1_CH6); also elsewhere on the board
VBUS: J3.A4 (VBUS), J3.A9 (VBUS), J3.B4 (VBUS), J3.B9 (VBUS); also elsewhere on the board
VDD: J1.3, J2.3; also elsewhere on the board
~RST: C14.1, R5.2, SW1.2, U3.3 (EN)

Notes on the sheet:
Power
Buttons
Jumper allows disabling of Power LED
33R is for LED strips where data and GND are wired together 220R is for runs where the data and PWR lines are in discrete wires
This design uses power planes, so the current limit is primarily set by what the DC jack and terminal blocks can handle, and then obviously by the fuse value. Most "normal" versions of these parts seem to specify around 8-10A, so that's what the standard fuse value is set to. You can probably push 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
LED 2 Strip Output
LED 1 Strip Output
ESP Status LED
Power Status LED
USB
Optional MEMS Microphone
ORDER: screw termnals
- relay doesn't do anything - fix unconnected ground plane - can't use both channels at once? - random reboots and crashes - power supply issues? - crashes - will just crash, LEDs will stay on and can't connect it at all - think this is PSU issues. voltage goes really low on 3v3 line

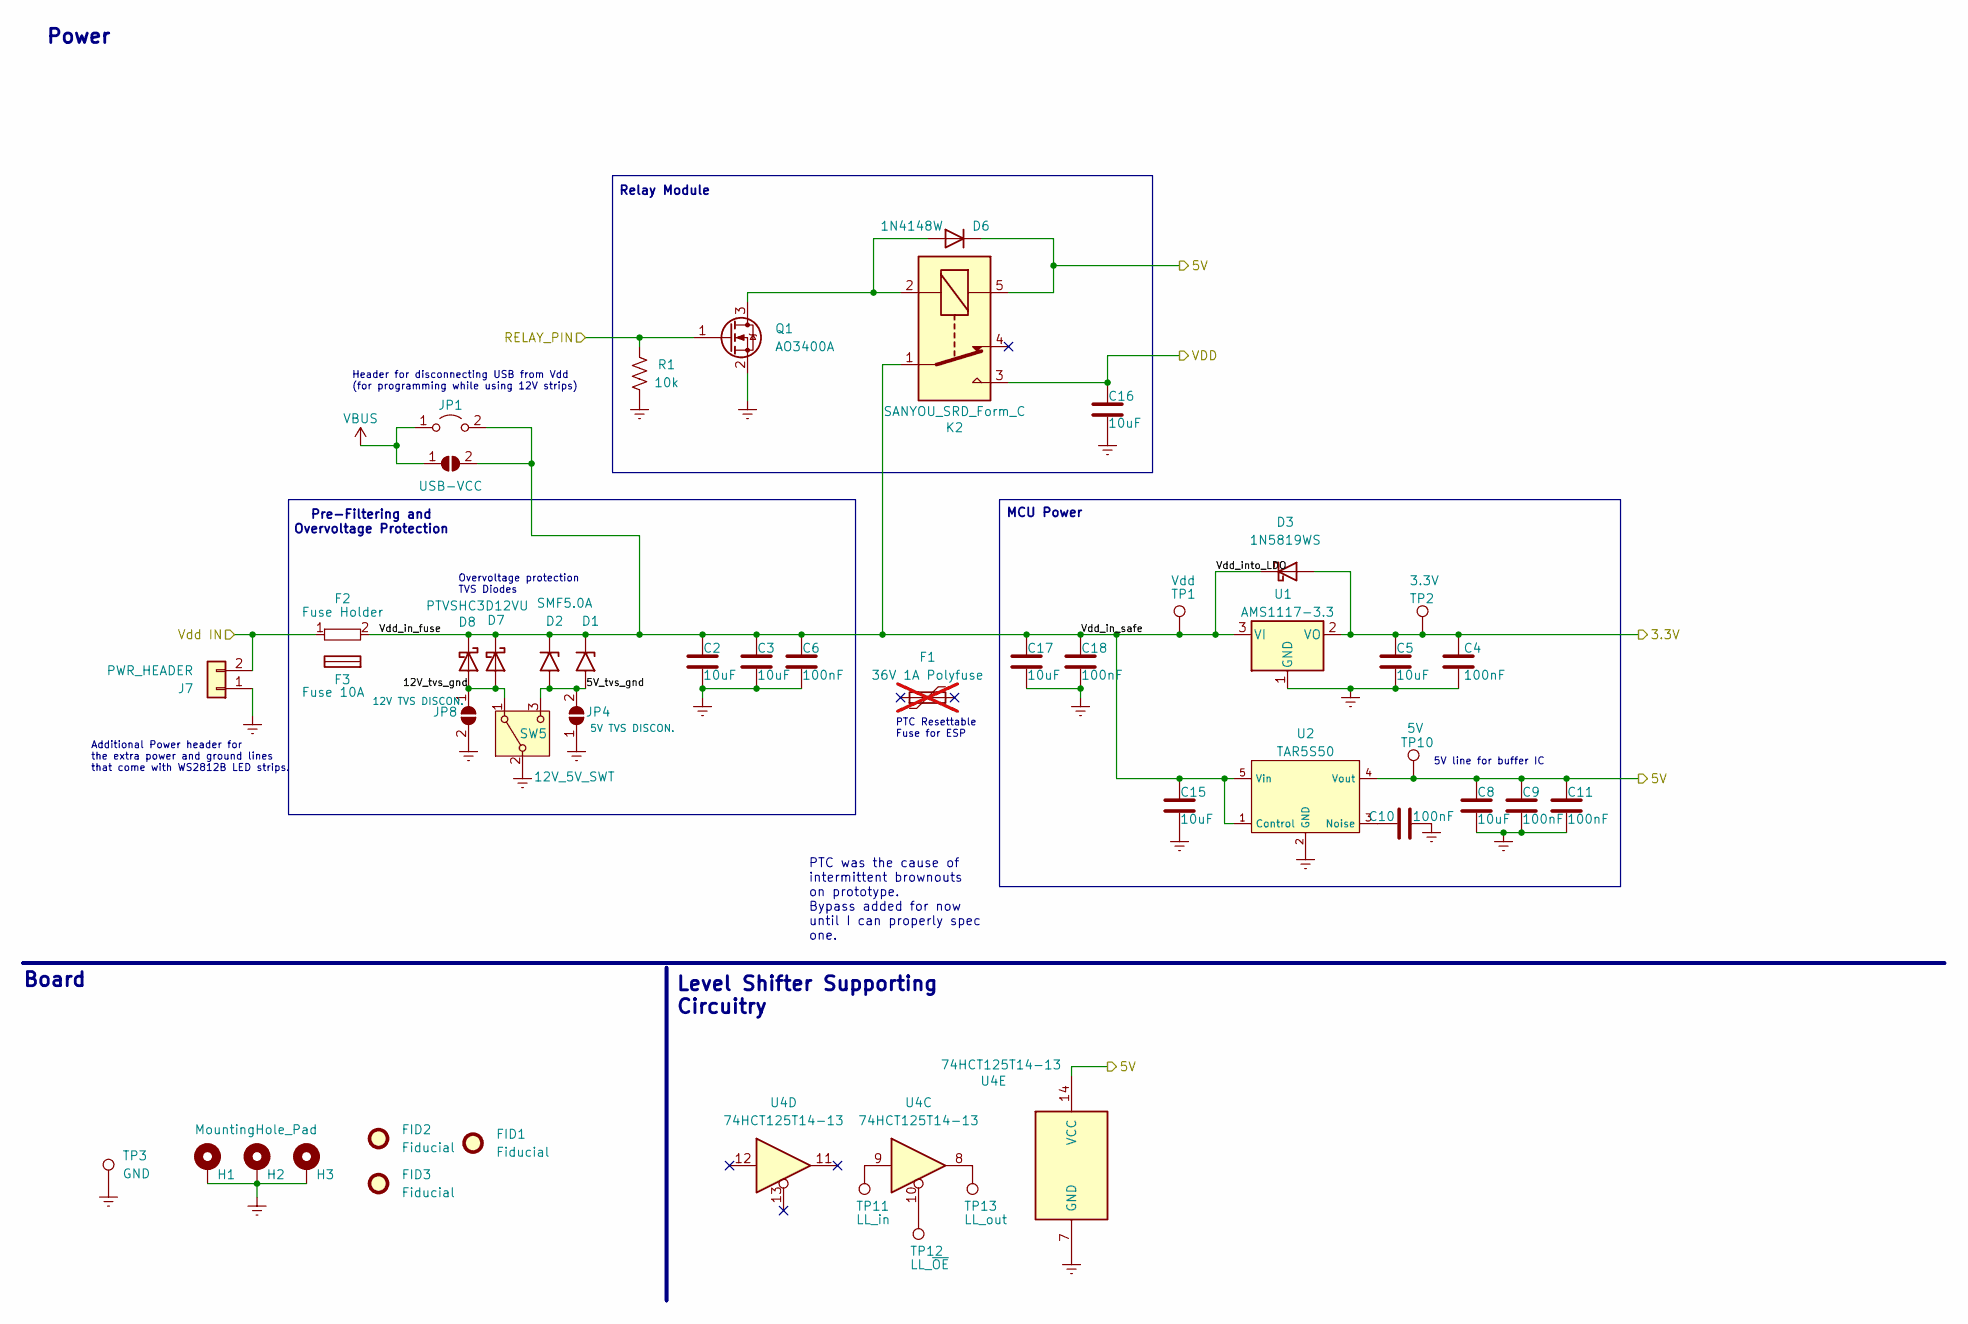
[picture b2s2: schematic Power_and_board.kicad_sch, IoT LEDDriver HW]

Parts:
C2, C3, C5, C8, C15, C16, C17: 10uF; C_0805_2012Metric_Pad1.18x1.45mm_HandSolder; LCSC C15850
C4, C6, C9, C10, C11, C18: 100nF; C_0805_2012Metric_Pad1.18x1.45mm_HandSolder; LCSC C49678
D1, D2: SMF5.0A; D_SMF; LCSC C20883238
D3: 1N5819WS; D_SOD-323_HandSoldering; LCSC C191023
D6: 1N4148W; D_SOD-123; LCSC C81598
D7, D8: PTVSHC3D12VU; D_SOD-323_HandSoldering; LCSC C169336
F1: 36V 1A Polyfuse; Fuse_1206_3216Metric_Pad1.42x1.75mm_HandSolder; LCSC C20616702; not fitted
F2: Fuse Holder; FUSE-TH_XF-505P; LCSC C843270
F3: Fuse 10A
FID1, FID2, FID3: Fiducial; Fiducial_0.5mm_Mask1mm
H1, H2, H3: MountingHole_Pad; MountingHole_2.2mm_M2_Pad_Via
J7: PWR_HEADER; SolderWire-0.5sqmm_1x02_P4.6mm_D0.9mm_OD2.1mm
JP1: USB-VDD; TestPoint_2Pads_Pitch2.54mm_Drill0.8mm
JP3: USB-VCC; SolderJumper-2_P1.3mm_Open_RoundedPad1.0x1.5mm
JP4: 5V TVS DISCON.; SolderJumper-2_P1.3mm_Open_RoundedPad1.0x1.5mm
JP8: 12V TVS DISCON.; SolderJumper-2_P1.3mm_Open_RoundedPad1.0x1.5mm
K2: SANYOU_SRD_Form_C; Relay_SPDT_SANYOU_SRD_Series_Form_C; LCSC C35449
Q1: AO3400A; SOT-23_Handsoldering; LCSC C20917
R1: 10k; R_0805_2012Metric_Pad1.20x1.40mm_HandSolder; LCSC C17414
SW5: 12V_5V_SWT; SW_SPDT_PCM12; LCSC C319020
TP1: Vdd; TestPoint_Pad_D1.5mm
TP2: 3.3V; TestPoint_Pad_D1.5mm
TP3: GND; TestPoint_Pad_D1.5mm
TP10: 5V; TestPoint_Pad_D1.5mm
TP11: LL_in; TestPoint_Pad_D1.0mm
TP12: LL_~{OE}; TestPoint_Pad_D1.0mm
TP13: LL_out; TestPoint_Pad_D1.0mm
U1: AMS1117-3.3; SOT-223-3_TabPin2; LCSC C6186
U2: TAR5S50; SSOP-5_L2.9-W1.6-P0.95-LS2.8-TL; LCSC C146354
U4: 74HCT125T14-13; TSSOP-14_4.4x5mm_P0.65mm; LCSC C842453

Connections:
+3.3V: C4.1, C5.1, D3.2 (A), TP2.1, U1.2 (VO); also elsewhere on the board
+5V: C8.1, C9.1, C11.1, D6.1 (K), K2.5, TP10.1, U2.4 (Vout), U4.14 (VCC)
/Power_and_board/5V_tvs_gnd: D1.2 (A2), D2.2 (A2), JP4.2 (B), SW5.3 (C)
/Power_and_board/12V_tvs_gnd: D7.2 (A), D8.2 (A), JP8.1 (A), SW5.1 (A)
/Power_and_board/Vdd IN: F2.1, J7.2; also elsewhere on the board
/Power_and_board/Vdd_in_fuse: C2.1, C3.1, C6.1, C15.1, C17.1, C18.1, D1.1 (A1), D2.1 (A1), D3.1 (K), D7.1 (K), D8.1 (K), F2.2, JP1.2 (B), JP3.2 (B), K2.1, TP1.1, U1.3 (VI), U2.1 (Control), U2.5 (Vin)
Earth: C2.2, C3.2, C4.2, C5.2, C6.2, C8.2, C9.2, C10.2, C11.2, C15.2, C16.2, C17.2, C18.2, H1.1, H2.1, H3.1, J7.1, JP4.1 (A), JP8.2 (B), Q1.2 (S), R1.1, SW5.2 (B), TP3.1, U1.1 (GND), U2.2 (GND), U4.7 (GND); also elsewhere on the board
unnamed: D6.2 (A), K2.2, Q1.3 (D)
unnamed: TP11.1, U4.9
unnamed: TP12.1, U4.10
unnamed: TP13.1, U4.8
unnamed: C10.1, U2.3 (Noise)
RELAY_PIN: Q1.1 (G), R1.2; also elsewhere on the board
VBUS: JP1.1 (A), JP3.1 (A); also elsewhere on the board
VDD: C16.1, K2.3; also elsewhere on the board

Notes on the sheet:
5V line for buffer IC
Overvoltage protection TVS Diodes
Relay Module
MCU Power
Header for disconnecting USB from Vdd (for programming while using 12V strips)
Pre-Filtering and Overvoltage Protection
PTC Resettable Fuse for ESP
Board
Additional Power header for the extra power and ground lines that come with WS2812B LED strips.
Power
Level Shifter Supporting Circuitry
PTC was the cause of intermittent brownouts on prototype. Bypass added for now until I can properly spec one.
